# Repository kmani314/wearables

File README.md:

# wearables
First thing is a fitness watch:
* Using nRF52840 as the SOC, includes BT on chip
    * This version will not have WiFi
* MAX32664 and MAX86141 for heart rate, pulse oximetry, associated LEDs and photodiode
* Small TFT LCD
* MAX77659 for power management
* Small Li-ion
* USB-C
Most of the maxim parts only come in really small WLCSP type packages, unclear if JLC can produce them or if they are hand-solderable with good repeatability.

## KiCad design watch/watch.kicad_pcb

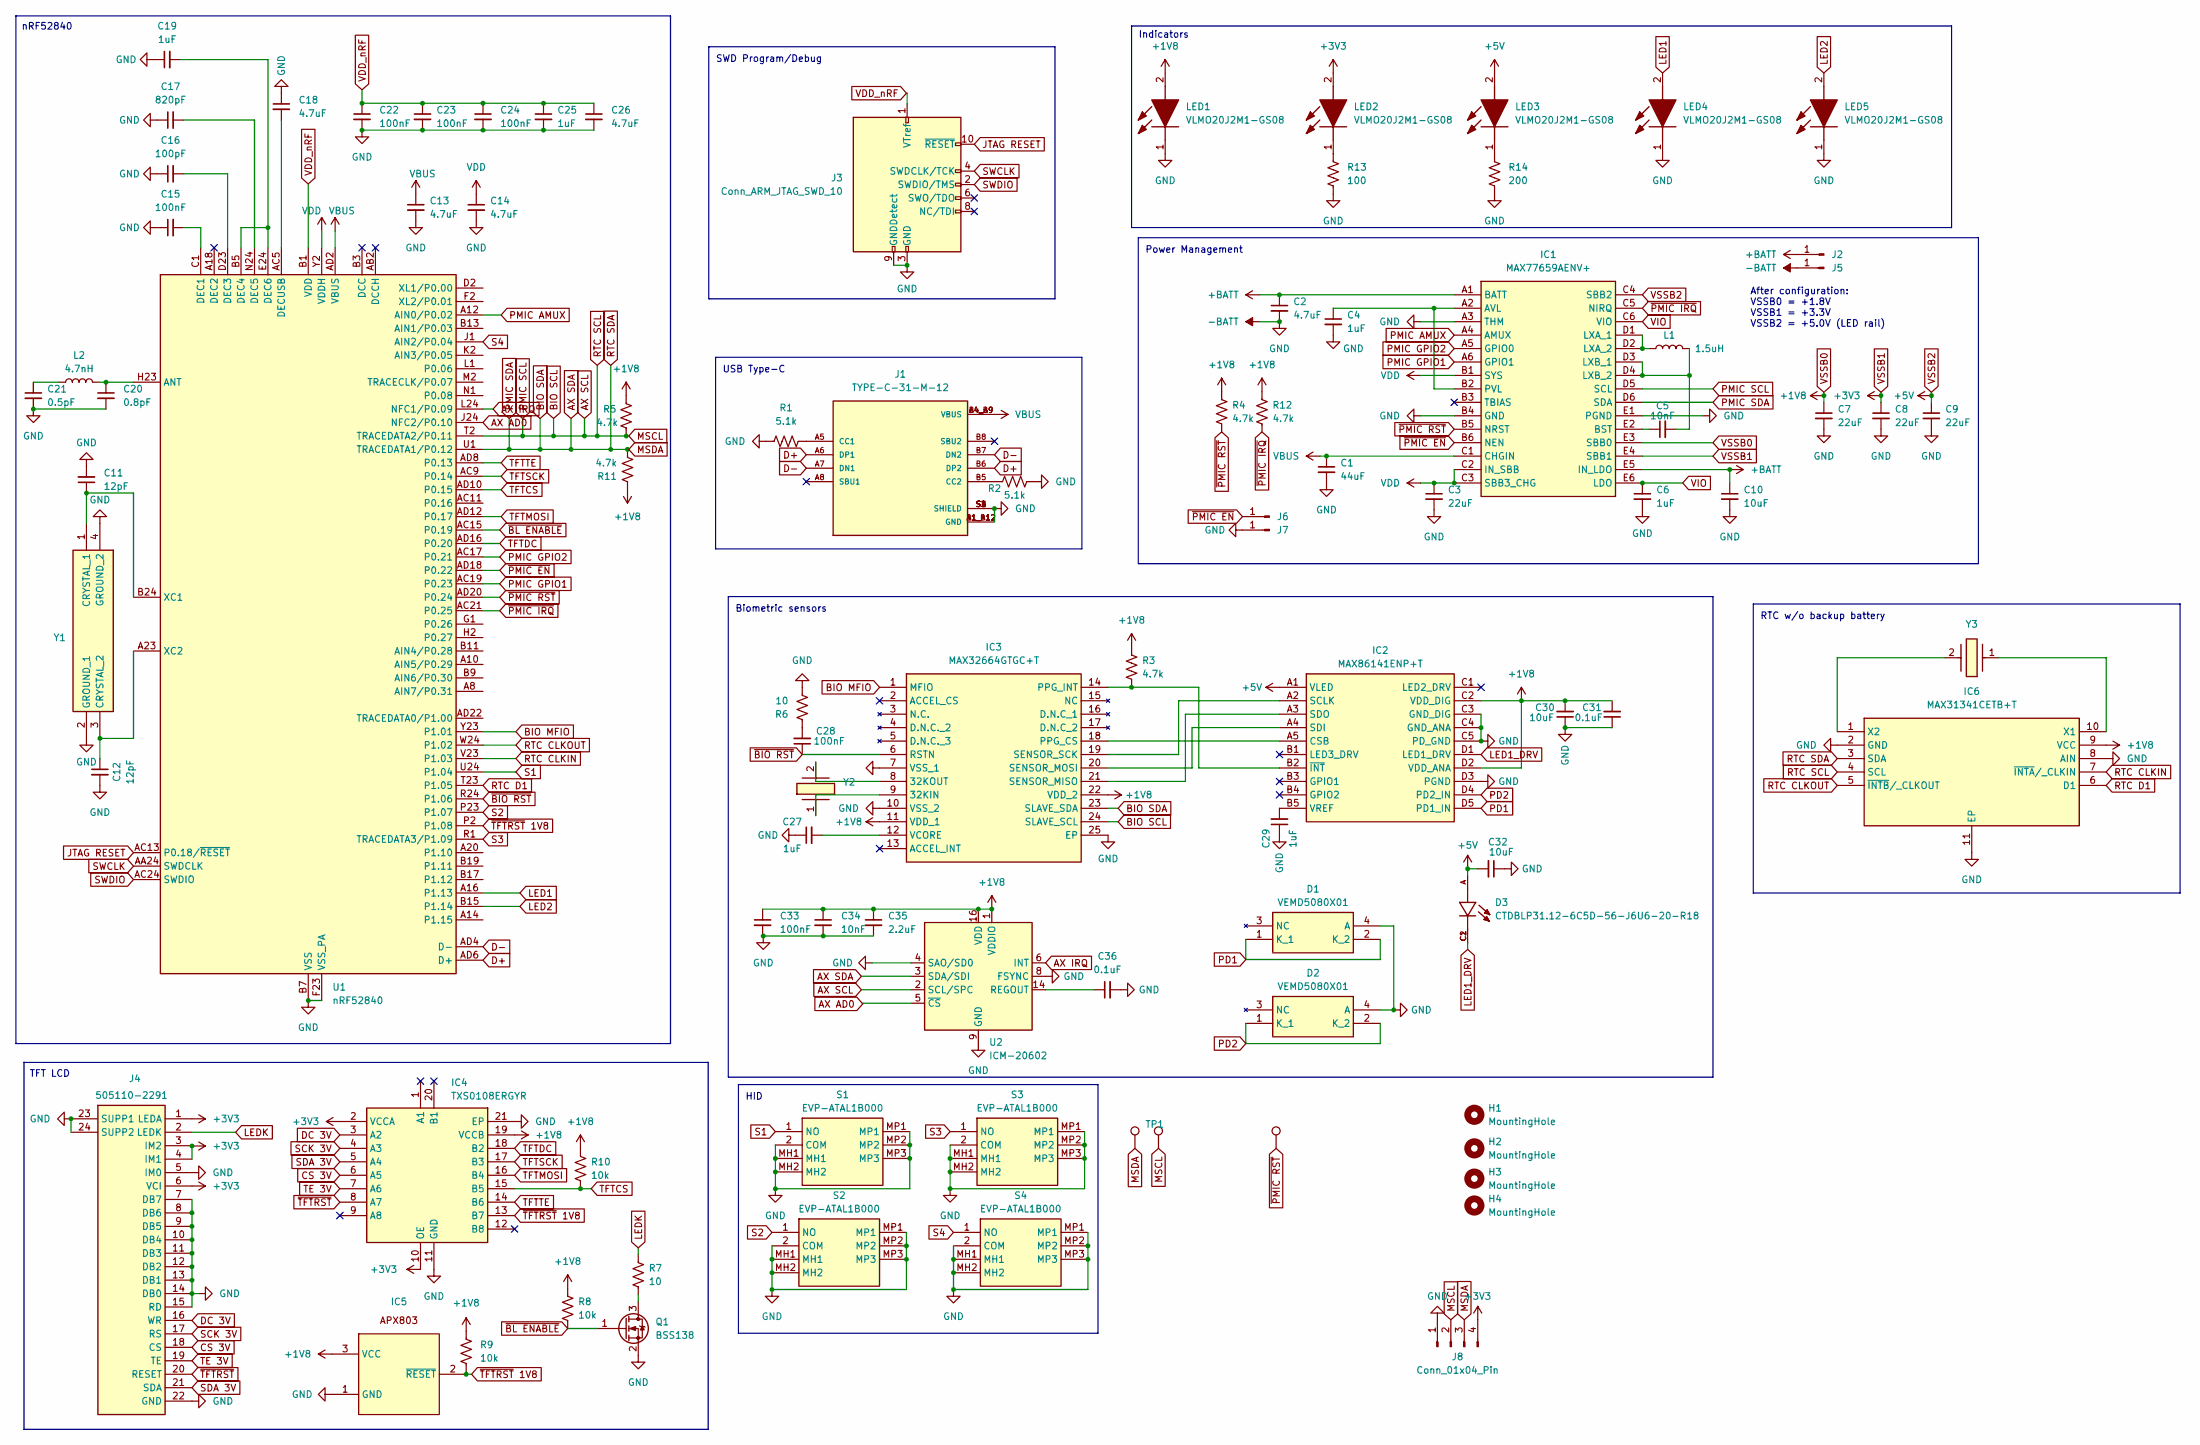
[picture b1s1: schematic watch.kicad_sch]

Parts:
C1: 44uF; C_0603_1608Metric_Pad1.08x0.95mm_HandSolder
C2, C13, C14, C18, C26: 4.7uF; C_0603_1608Metric_Pad1.08x0.95mm_HandSolder
C3, C7, C8, C9: 22uF; C_0603_1608Metric_Pad1.08x0.95mm_HandSolder
C4, C6: 1uF; C_0402_1005Metric_Pad0.74x0.62mm_HandSolder
C5: 10nF; C_0201_0603Metric_Pad0.64x0.40mm_HandSolder
C10, C30, C32: 10uF; C_0603_1608Metric_Pad1.08x0.95mm_HandSolder
C11, C12: 12pF; C_0402_1005Metric_Pad0.74x0.62mm_HandSolder
C15, C22, C23, C24, C28, C33: 100nF; C_0402_1005Metric_Pad0.74x0.62mm_HandSolder
C16: 100pF; C_0402_1005Metric_Pad0.74x0.62mm_HandSolder
C17: 820pF; C_0402_1005Metric_Pad0.74x0.62mm_HandSolder
C19, C25, C27, C29: 1uF; C_0603_1608Metric_Pad1.08x0.95mm_HandSolder
C20: 0.8pF; C_0402_1005Metric_Pad0.74x0.62mm_HandSolder
C21: 0.5pF; C_0402_1005Metric_Pad0.74x0.62mm_HandSolder
C31, C36: 0.1uF; C_0402_1005Metric_Pad0.74x0.62mm_HandSolder
C34: 10nF; C_0402_1005Metric_Pad0.74x0.62mm_HandSolder
C35: 2.2uF; C_0603_1608Metric_Pad1.08x0.95mm_HandSolder
D1, D2: VEMD5080X01; Mouser Part Number 78-VEMD5080X01
D3: CTDBLP31.12-6C5D-56-J6U6-20-R18; LED_CTDBLP31.12-6C5D-56-J6U6-20-R18; PARTREV 1.2
H1, H2, H3, H4: MountingHole; watch-housing
IC1: MAX77659AENV+; BGA30C40P6X5_255X237X50; Mouser Part Number 700-MAX77659AENV+
IC2: MAX86141ENP+T; BGA20C40P5X4_205X185X50; Mouser Part Number 700-MAX86141ENP+T
IC3: MAX32664GTGC+T; MAX32664GTGC; Mouser Part Number 700-MAX32664GTGC+T
IC4: TXS0108ERGYR; SN74LVC541ARGYR; Mouser Part Number 595-TXS0108ERGYR
IC5: SOT-23-3
IC6: MAX31341CETB+T; SON50P300X300X80-11N; Mouser Part Number 700-MAX31341CETB+T
J1: TYPE-C-31-M-12; HRO_TYPE-C-31-M-12; PARTREV 2020.12.08
J2, J5: Conn_01x01_Pin; TestPoint_Pad_4.0x4.0mm
J3: Conn_ARM_JTAG_SWD_10; Tag-Connect_TC2050-IDC-FP_2x05_P1.27mm_Vertical
J4: 505110-2291; 5051102291; Mouser Part Number 538-505110-2291
J6, J7: Conn_01x01_Pin; TestPoint_Pad_1.5x1.5mm
J8: Conn_01x04_Pin; PinHeader_1x04_P2.54mm_Vertical
L1: 1.5uH; L_0603_1608Metric_Pad1.05x0.95mm_HandSolder
L2: 4.7nH; L_0402_1005Metric_Pad0.77x0.64mm_HandSolder
LED1, LED2, LED3, LED4, LED5: VLMO20J2M1-GS08; LEDM2214X140N; Mouser Part Number 78-VLMO20J2M1
Q1: BSS138; SOT-23
R1, R2: 5.1k; R_0201_0603Metric_Pad0.64x0.40mm_HandSolder
R3, R4, R5, R11, R12: 4.7k; R_0201_0603Metric_Pad0.64x0.40mm_HandSolder
R6: 10; R_0201_0603Metric_Pad0.64x0.40mm_HandSolder
R7: 10; R_0805_2012Metric_Pad1.20x1.40mm_HandSolder
R8, R9, R10: 10k; R_0201_0603Metric_Pad0.64x0.40mm_HandSolder
R13: 100; R_0805_2012Metric_Pad1.20x1.40mm_HandSolder
R14: 200; R_0805_2012Metric_Pad1.20x1.40mm_HandSolder
S1, S2, S3, S4: EVP-ATAL1B000; EVPATAL1B000; Mouser Part Number 667-EVP-ATAL1B000
TP1, TP2, TP15: TestPoint; TestPoint_Pad_D1.0mm
U1: nRF52840; Nordic_AQFN-73-1EP_7x7mm_P0.5mm
U2: ICM-20602; LGA-16_3x3mm_P0.5mm_LayoutBorder3x5y
Y1: FA-128_32.0000MF10Z-AJ5; FA128320000MF10ZAJ5; Mouser Part Number 732-FA-12832MF10ZAJ5
Y2, Y3: CM7V-T1A-32.768kHz-6pF-20PPM-TA-QC; CM7V32768TBQA020; Mouser Part Number 428-201843-MG01

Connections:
+BATT: C2.1, C10.1, IC1.A1 (BATT), IC1.E5 (IN_LDO), J2.1
-BATT: C1.2, C2.2, C3.2, C4.2, C6.2, C7.2, C8.2, C9.2, C10.2, C11.2, C12.2, C13.2, C14.2, C15.1, C16.1, C17.1, C18.1, C19.1, C20.2, C21.2, C22.2, C23.2, C24.2, C25.2, C26.2, C27.1, C29.1, C30.1, C31.1, C32.1, C33.2, C34.2, C35.2, C36.2, D1.4 (A), D2.4 (A), IC1.A3 (THM), IC1.B4 (GND), IC1.E1 (PGND), IC2.C3 (GND_DIG), IC2.C4 (GND_ANA), IC2.C5 (PD_GND), IC2.D3 (PGND), IC3.7 (VSS_1), IC3.10 (VSS_2), IC3.25 (EP), IC4.11 (GND), IC4.21 (EP), IC5.1 (GND), IC6.2 (GND), IC6.8 (AIN), IC6.11 (EP), J1.A1_B12 (GND), J1.B1_A12 (GND), J1.S1 (SHIELD), J1.S2 (SHIELD), J1.S3 (SHIELD), J1.S4 (SHIELD), J3.3 (GND), J3.5 (GND), J3.9 (GNDDetect), J4.5 (IM0), J4.7 (DB7), J4.8 (DB6), J4.9 (DB5), J4.10 (DB4), J4.11 (DB3), J4.12 (DB2), J4.13 (DB1), J4.14 (DB0), J4.15 (RD), J4.22 (GND), J4.23 (SUPP1), J4.24 (SUPP2), J5.1, J7.1, J8.1, LED1.1 (K), LED4.1 (K), LED5.1 (K), Q1.2 (S), R1.1, R2.1, R6.1, R13.2, R14.2, S1.2 (COM), S1.MH1, S1.MH2, S1.MP1, S1.MP2, S1.MP3, S2.2 (COM), S2.MH1, S2.MH2, S2.MP1, S2.MP2, S2.MP3, S3.2 (COM), S3.MH1, S3.MH2, S3.MP1, S3.MP2, S3.MP3, S4.2 (COM), S4.MH1, S4.MH2, S4.MP1, S4.MP2, S4.MP3, U1.B7 (VSS), U1.EP (VSS), U1.F23 (VSS_PA), U2.4 (SAO/SD0), U2.8 (FSYNC), U2.9 (GND), U2.10 (GND), U2.11 (GND), U2.12 (GND), U2.13 (GND), U2.15 (GND), Y1.2 (GROUND_1), Y1.4 (GROUND_2)
AX AD0: U1.J24 (NFC2/P0.10), U2.5 (~CS)
AX IRQ: U1.L24 (NFC1/P0.09), U2.6 (INT)
AX SCL: IC1.D5 (SCL), IC3.24 (SLAVE_SCL), IC6.4 (SCL), J8.2, R5.2, TP2.1, U1.T2 (TRACEDATA2/P0.11), U2.2 (SCL/SPC)
AX SDA: IC1.D6 (SDA), IC3.23 (SLAVE_SDA), IC6.3 (SDA), J8.3, R11.2, TP1.1, U1.U1 (TRACEDATA1/P0.12), U2.3 (SDA/SDI)
BIO MFIO: IC3.1 (MFIO), U1.Y23 (P1.01)
CS 3V: IC4.6 (A5), J4.18 (CS)
D+: J1.A6 (DP1), J1.B6 (DP2), U1.AD6 (D+)
D-: J1.A7 (DN1), J1.B7 (DN2), U1.AD4 (D-)
DC 3V: IC4.3 (A2), J4.16 (WR)
JTAG RESET: J3.10 (~RESET), U1.AC13 (P0.18/~RESET)
LED1: LED4.2 (A), U1.A16 (P1.13)
LED1_DRV: D3.C1, D3.C2, IC2.D1 (LED1_DRV)
LED2: LED5.2 (A), U1.B15 (P1.14)
LEDK: J4.2 (LEDK), R7.1
unnamed: C21.1, L2.1
unnamed: C28.2, R6.2
unnamed: C4.1, IC1.A2 (AVL), IC1.B2 (PVL)
unnamed: C5.1, IC1.E2 (BST)
unnamed: IC1.D1 (LXA_1), IC1.D2 (LXA_2), L1.1
unnamed: C5.2, IC1.D3 (LXB_1), IC1.D4 (LXB_2), L1.2
unnamed: IC2.A5 (CSB), IC3.18 (PPG_CS)
unnamed: IC2.A2 (SCLK), IC3.19 (SENSOR_SCK)
unnamed: IC2.A4 (SDI), IC3.20 (SENSOR_MOSI)
unnamed: IC2.A3 (SDO), IC3.21 (SENSOR_MISO)
unnamed: C29.2, IC2.B5 (VREF)
unnamed: IC2.B2 (~INT), IC3.14 (PPG_INT), R3.2
unnamed: IC3.9 (32KIN), Y2.1
unnamed: IC3.8 (32KOUT), Y2.2
unnamed: C27.2, IC3.12 (VCORE)
unnamed: IC6.10 (X1), Y3.1
unnamed: IC6.1 (X2), Y3.2
unnamed: J1.A5 (CC1), R1.2
unnamed: J1.B5 (CC2), R2.2
unnamed: LED2.1 (K), R13.1
unnamed: LED3.1 (K), R14.1
unnamed: Q1.3 (D), R7.2
unnamed: C20.1, L2.2, U1.H23 (ANT)
unnamed: C15.2, U1.C1 (DEC1)
unnamed: C16.2, U1.D23 (DEC3)
unnamed: C19.2, U1.B5 (DEC4), U1.E24 (DEC6)
unnamed: C17.2, U1.N24 (DEC5)
unnamed: C18.2, U1.AC5 (DECUSB)
unnamed: C11.1, U1.B24 (XC1), Y1.1 (CRYSTAL_1)
unnamed: C12.1, U1.A23 (XC2), Y1.3 (CRYSTAL_2)
unnamed: C36.1, U2.14 (REGOUT)
PD1: D1.1 (K_1), D1.2 (K_2), IC2.D5 (PD1_IN)
PD2: D2.1 (K_1), D2.2 (K_2), IC2.D4 (PD2_IN)
PMIC AMUX: IC1.A4 (AMUX), U1.A12 (AIN0/P0.02)
PMIC GPIO1: IC1.A6 (GPIO1), U1.AC19 (P0.23)
PMIC GPIO2: IC1.A5 (GPIO0), U1.AC17 (P0.21)
RTC CLKIN: IC6.7 (~INTA/_CLKIN), U1.V23 (P1.03)
RTC CLKOUT: IC6.5 (~INTB/_CLKOUT), U1.W24 (P1.02)
RTC D1: IC6.6 (D1), U1.T23 (P1.05)
S1: S1.1 (NO), U1.U24 (P1.04)
S2: S2.1 (NO), U1.P23 (P1.07)
S3: S3.1 (NO), U1.R1 (TRACEDATA3/P1.09)
S4: S4.1 (NO), U1.J1 (AIN2/P0.04)
SCK 3V: IC4.4 (A3), J4.17 (RS)
SDA 3V: IC4.5 (A4), J4.21 (SDA)
SWCLK: J3.4 (SWDCLK/TCK), U1.AA24 (SWDCLK)
SWDIO: J3.2 (SWDIO/TMS), U1.AC24 (SWDIO)
TE 3V: IC4.7 (A6), J4.19 (TE)
TFTCS: IC4.15 (B5), R10.2, U1.AD10 (P0.15)
TFTDC: IC4.18 (B2), U1.AD16 (P0.20)
TFTMOSI: IC4.16 (B4), U1.AD12 (P0.17)
TFTSCK: IC4.17 (B3), U1.AC9 (P0.14)
TFTTE: IC4.14 (B6), U1.AD8 (P0.13)
VBUS: C1.1, C13.1, IC1.C1 (CHGIN), J1.A4_B9 (VBUS), J1.B4_A9 (VBUS), U1.AD2 (VBUS)
VDD: C3.1, C14.1, IC1.B1 (SYS), IC1.C2 (IN_SBB), IC1.C3 (SBB3_CHG), U1.Y2 (VDDH)
VDD_nRF: C22.1, C23.1, C24.1, C25.1, C26.1, J3.1 (VTref), U1.A22 (VDD), U1.AD14 (VDD), U1.AD23 (VDD), U1.B1 (VDD), U1.W1 (VDD)
VIO: C6.1, IC1.C6 (VIO), IC1.E6 (LDO)
VSSB0: C7.1, C30.2, C31.2, C33.1, C34.1, C35.1, IC1.E3 (SBB0), IC2.C2 (VDD_DIG), IC2.D2 (VDD_ANA), IC3.11 (VDD_1), IC3.22 (VDD_2), IC4.19 (VCCB), IC5.3 (VCC), IC6.9 (VCC), LED1.2 (A), R3.1, R4.1, R5.1, R8.1, R9.1, R10.1, R11.1, R12.1, U2.1 (VDDIO), U2.16 (VDD)
VSSB1: C8.1, IC1.E4 (SBB1), IC4.2 (VCCA), IC4.10 (OE), J4.1 (LEDA), J4.3 (IM2), J4.4 (IM1), J4.6 (VCI), J8.4, LED2.2 (A)
VSSB2: C9.1, C32.2, D3.A, IC1.C4 (SBB2), IC2.A1 (VLED), LED3.2 (A)
~BIO RST: C28.1, IC3.6 (RSTN), U1.R24 (P1.06)
~BL ENABLE: Q1.1 (G), R8.2, U1.AC15 (P0.19)
~PMIC EN: IC1.B6 (NEN), J6.1, U1.AD18 (P0.22)
~PMIC IRQ: IC1.C5 (NIRQ), R12.2, U1.AC21 (P0.25)
~PMIC RST: IC1.B5 (NRST), R4.2, TP15.1, U1.AD20 (P0.24)
~TFTRST: IC4.8 (A7), J4.20 (RESET)
~TFTRST 1V8: IC4.13 (B7), IC5.2 (~RESET), R9.2, U1.P2 (P1.08)

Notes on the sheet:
SWD Program/Debug
Power Management
RTC w/o backup battery
After configuration: VSSB0 = +1.8V VSSB1 = +3.3V VSSB2 = +5.0V (LED rail)
HID
TFT LCD
nRF52840
USB Type-C
Indicators
Biometric sensors

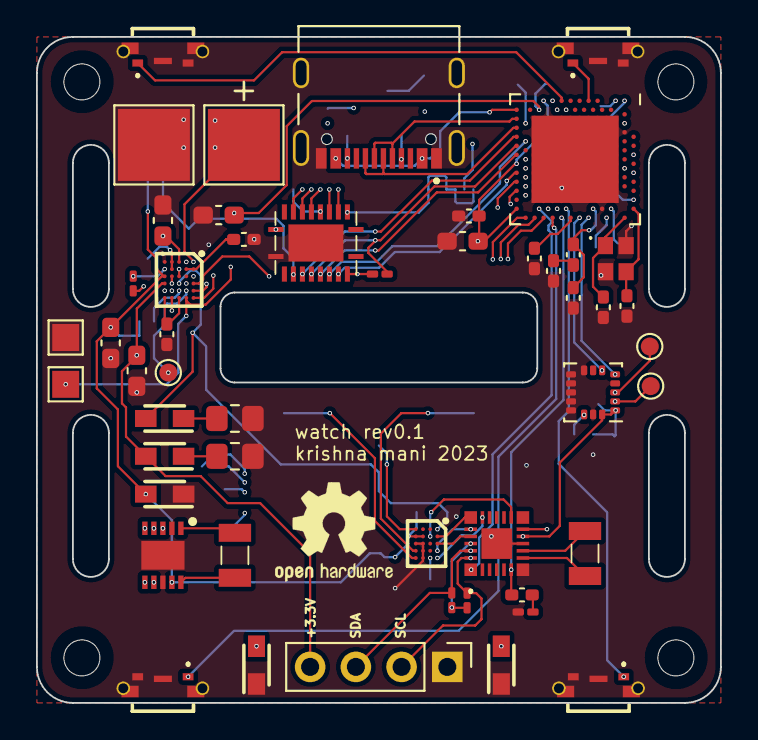
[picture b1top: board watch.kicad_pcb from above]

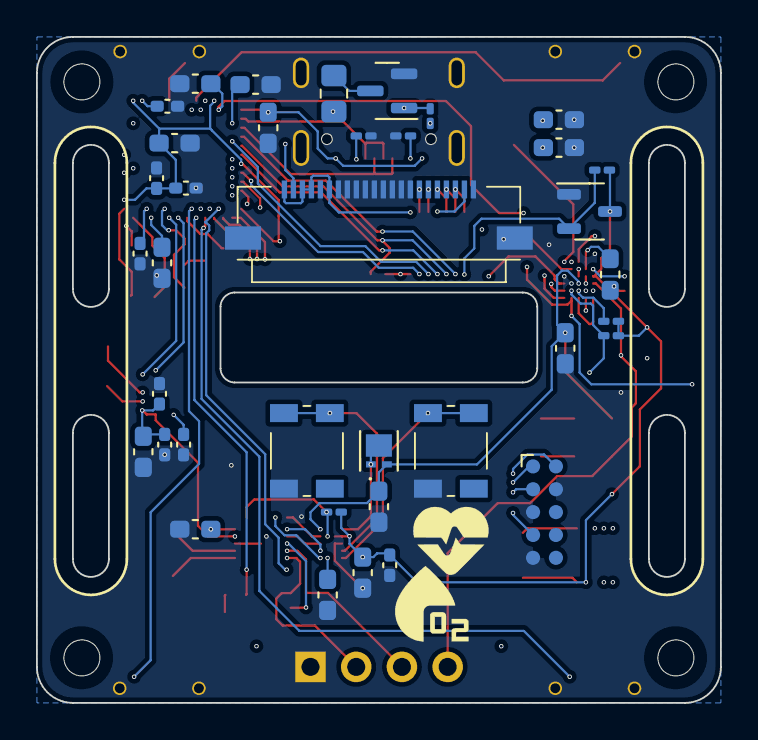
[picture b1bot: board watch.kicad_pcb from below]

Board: 4 copper layers, 38.0 x 37.0 mm, 91 parts (37 on the bottom side), 83 nets.

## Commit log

2023-06-06 read me
2023-06-08 lots of stuff: power management, uC power, USB
2023-06-08 organize and add display block, going to the gym
2023-06-09 first rev done
2023-06-11 parts finalized, started routing
2023-06-13 RTC, board started
2023-06-16 rev1 done absolutely does not pass drc need to add ci
2023-06-16 rev0.1 done, passes drc and jlc checks
2023-06-17 change mounting clearances, add expansion connector
